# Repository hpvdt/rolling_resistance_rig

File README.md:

# Rolling Resistance Rig (RRR)

One of the most crucial aspects of our land vehicles is the study of rolling resistance and our pursuit of reducing it. To this end the team has constucted a rolling resistance rig (_RRR_) to characterize different wheels. This repository serves as **the definitive** collection of information related to the RRR and its tests: especially the sensor system design and data processing. 

The general principle of the RRR is that there is a large drum which acts as the riding surface for the wheel and is spun up to speed by an electric motor to simulate speeds of over 80 km/h. The wheel under test is installed above the wheel and is loaded to a similar level to the expected vehicle load prior to the drum getting spun up. Once the desired speed is achieved by the system, the power to the drum is cut and the drum/wheel combo is left to slow down by dissipating power primarily through their own rolling resistances.

During this slowdown the rotational period of each part is monitored and recorded over serial to then be analyzed and derive a rolling resistance for the wheel being tested. This processing is performed after the experiment is concluded in MATLAB.

The exact procedure for this process is outlined in a separate markdown file, [`test_procedure.md`](./test_procedure.md).

## Repository Organization

There are a few folders used to sort the different components of the system.

| Folder | Purpose |
| --- | ---|
| `analysis` | Primarily the MATLAB files used to process the data collected |
| `analysis/data` | Previously collected experiment data |
| `arduino` | Microcontroller code used to collect data. **USE THE `rolling_resistance` SKETCH!** |
| `doc` | Assorted documentation about the system design |
| `hardware` | Hardware files for custom circuit boards designed for this system |

## Software Used

A few programs are needed to fully operate the system. No additional configuration is needed to any of the software to run the system (e.g. installing custom libraries).

- **Arduino IDE** (**V 2.1.0** as of writting) for programming the microntrollers used (Arduino Nanos/Unos).
- **KiCad 7** for the most recent board's hardware files. The previous version was prepared in EAGLE.
- **MATLAB** for post-processing of the data collected.
- **Excel/LibreOffice Calc** to store some results.

## Future Improvements

- [ ] Record procedure to determine inertia characteristics of a wheel as part of this repository
- [ ] Improve the data processing scripts. *More information in its [readme](analysis/readme.md).*

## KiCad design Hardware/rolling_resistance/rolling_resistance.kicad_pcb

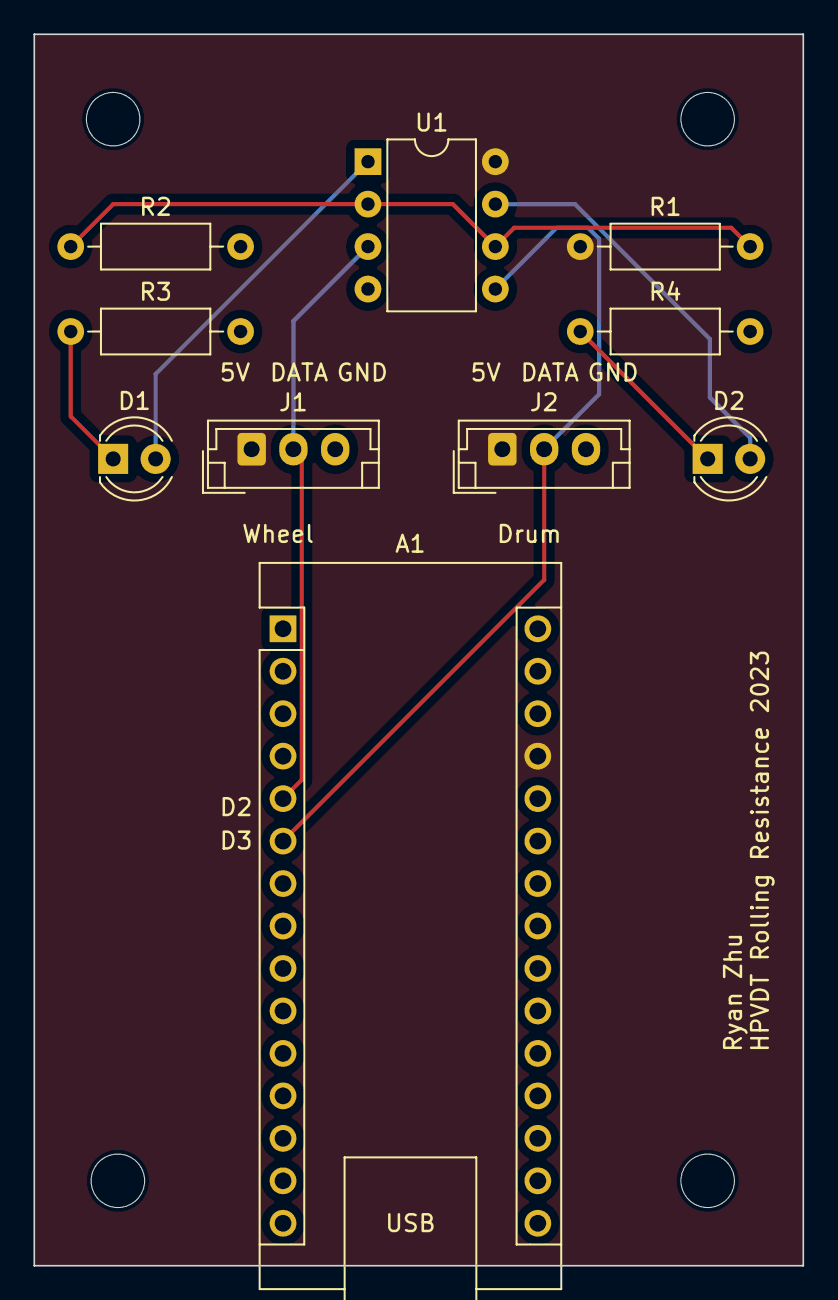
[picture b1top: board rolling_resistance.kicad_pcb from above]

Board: 2 copper layers, 46.0 x 73.7 mm, 10 parts (0 on the bottom side), 9 nets.

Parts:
A1: Arduino_Nano_v3.x; Arduino_Nano
D1, D2: LED; LED_D4.0mm
J1, J2: Conn_01x03; JST_EH_B3B-EH-A_1x03_P2.50mm_Vertical
R1, R2: 10K; R_Axial_DIN0207_L6.3mm_D2.5mm_P10.16mm_Horizontal
R3, R4: 330; R_Axial_DIN0207_L6.3mm_D2.5mm_P10.16mm_Horizontal
U1: LM358; DIP-8_W7.62mm

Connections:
+5V: A1.27 (+5V), J1.1, J2.1, R1.1, U1.8 (V+)
/LOWER: A1.6 (D3), J2.2, U1.5 (+)
/REF: R1.2, R2.1, U1.2 (-), U1.6 (-)
/UPPER: A1.5 (D2), J1.2, U1.3 (+)
GND: A1.4 (GND), A1.29 (GND), J1.3, J2.3, R2.2, R3.2, R4.2, U1.4 (V-)
unnamed: D1.2 (A), U1.1
unnamed: D1.1 (K), R3.1
unnamed: D2.2 (A), U1.7
unnamed: D2.1 (K), R4.1

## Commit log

2021-06-06 Initial proposed hardware
2022-11-29 proof of concept rolling resistance arduino code
2023-01-18 Initial commit of revised hardware
2023-07-21 Added KiCad gitignore
2023-07-21 Updated hardware to what was ordered
2023-08-26 Renamed hardware folder to lowercase
2023-08-26 Initial upload of all arduino code
2023-08-26 Initial upload of analysis code as proved by Calvin R.
2023-08-26 Upload of previously collected data and documentation
2023-08-26 Removed DS_Store files
2023-08-26 Added general gitignore
2023-08-27 Tidied up formatting and outlined plan
2023-08-27 Updated to digital interrupts
    Previous code was based on analog sensors and polling. Switching to digital sensors and interrupts simplifies the code and improves the accuracy of timing events.
    Also deleted the previous version to not be confused for the "actively" developed version.
2023-08-27 Improved data output
    Enabling easy change of delimiter and float precision.
    Also changed code so that data is atomically copied for printing (can't be disturbed by interrupts).
2023-08-27 Updated readme's
2023-08-27 Cleaned up documentation
    Removed redundant documents and combined similar documents (primarily into "Master Plan" doc).
    Converted test notes into Markdown for easier version control and glancing.
2023-08-27 Updated processing to use CSVs for configuration
    Removed redundant Excel workbooks and added MATLAB .gitignore file
2023-08-27 Added circumference announcment to Arduino code
2023-08-27 Improved readmes related to post processing
2023-08-27 Unified naming scheme for collected data
    Also cleaned up some redundant data in the folder
2023-08-27 Deleted stshed and outdated `Power_tire.m`
2023-08-27 COnverted `info_test.csv` to csv
2023-08-27 Merged all inertia measurements into single folder
2023-08-27 Merged collected data into one directory
    Compared all both data sets deleting redundant copies and moving missing data to the MATLAB data folder.
    Also reduced the size of many Excel workbooks by deleting columns to the right of principle data.
2023-08-27 Relabelled data folders
    Reflected changes in MATLAB scripts while breaking the `cd` commands into parts to be OS agnostic.
    Also minorly improved MATLAB function documentation.
2023-08-27 Converted aero data to CSV format
    Will enable easier processing of data in other systems and save storage space
2023-08-27 Returned Drum inertia file as Excel workbook
2023-08-27 Renamed documentation folder
2023-08-27 Touched up main readme
2023-08-28 Changed delimiter to comma
2023-08-30 Properly updating `prevTime` in interrupts
2023-08-31 Clarification regarding the 'force' data
    Also converted the force data sets to .CSV.
2023-08-31 Recorded main experiment procedure
    Also elaborated on the related data collection requirements. Inertia test proceedure to be completed later.
2023-08-31 Changed file addressing scheme
    Data files are now addressed in the data directory. Previously the directories were navigated into using `cd` commands; this was a bt messy and annoying in the event of an error causing the script to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
2023-09-03 Uploaded Grandprix 406 measurements
    Tested 2nd September 2023 by Luke P. and Hannah D. Wheels described as "Continental Grand Prix 406 ERLKONIG 28 mm pressurized at 90 psi"
2023-09-06 Renamed Grandprix 406 wheels to reflect proper psi
2023-09-10 Cleaned up and commented drum curve script
2023-09-10 Trying to decipher `AGmean`
    It is only used at one point in inertia calculation, seems to be some mix of geometric and statistical means
2023-09-10 Ignoring MAC OS folders
2023-09-10 Removed last `xlsread`
2023-09-10 Cleaned inertia data
    Converted all `.txt`s to `.csv` and deleted the redundant ones which had `.xlsx` files
2023-09-10 Minor reformatting of `inertiaClac`
2023-09-11 Converted inertia data to `.csv` format
    Converted for better version control and reduced repository size. Also added a readme for the interia files.
2023-09-11 Simplified inertia recordings
    Previously all data had rows skipped due to how the sensors used to work on the rig, recording two event per rotation. Now the data and code assumes one event per rotation for easier interpretation o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
2023-09-11 Cleaned up figure creation for rolling resistance
    Moved much of the figure configuration outside the loop
2023-09-11 Removed unused variables
    Also cleared up some of the *very* specific testing code
2023-09-11 Simplified wheel data importing
2023-09-11 Renamed configuration file, moved test summary
2023-09-11 Added space before 'psi' in data file names
2023-09-11 Converted all scorcher references to be consistent
2023-09-11 Get permissible names from `wheelInfo.csv`
    This way adds the benefit make sure that there is inertia data for a wheel as well (since that's in `wheelInfo.csv`), not just speed data recorded.
2023-09-11 Find drum moment of inertia regardless of order
2023-09-11 Auto-legend, noted issues for multi-trials
    Current logic in `RRcalc.m` doesn't seem to properly account for multiple different wheels, with different pressure levels. **This MUST get addressed in the future!**
2023-09-12 Cleaned up commented code, removed unused parts
2023-09-12 Added header comments for supporting functions
2023-09-14 Create Raw_Data
    Added folder for dumping raw data from testing
2023-09-14 Delete analysis/data/aero/Raw_Data
    I don't know how to use GitHub
2023-09-14 Create raw-data
    New file for dumping pre-processed raw data into from testing
2023-09-14 Added completed pre-processed tests
2023-09-14 Add files via upload
    added 60 psi partially completed tests
2023-09-23 Converted Continental files to .csv
2023-09-23 describes test data format to understand spreadsheets
    trying to edit readmes
2023-09-23 Updated inertia readme
    clarified what coin is
    Set personal goals to figure out this code
2023-10-28 Update Drum_I1.csv
    unscrewing up the excel file i screwed up
2023-10-28 Rieder's I Calculation Changes
    1. Tweaked M, R, and added brackets in Iwheel based on Rieder's calculation (see end of file)
    2. Removed theta2, r_coin unused variables.
    3. updated RRcalc.m to use new InertiaCalc.m
    The new I numbers are pretty similar to the old ones yay!!
2023-11-11 Cleaned up inertia calculation with info
    - updated readme with basic test info
    - cleaned up InertiaCalc+rrcalc file
2023-11-11 add reference calculations
2024-02-03 Slightly clarify rolling resistance inertia collection readme
